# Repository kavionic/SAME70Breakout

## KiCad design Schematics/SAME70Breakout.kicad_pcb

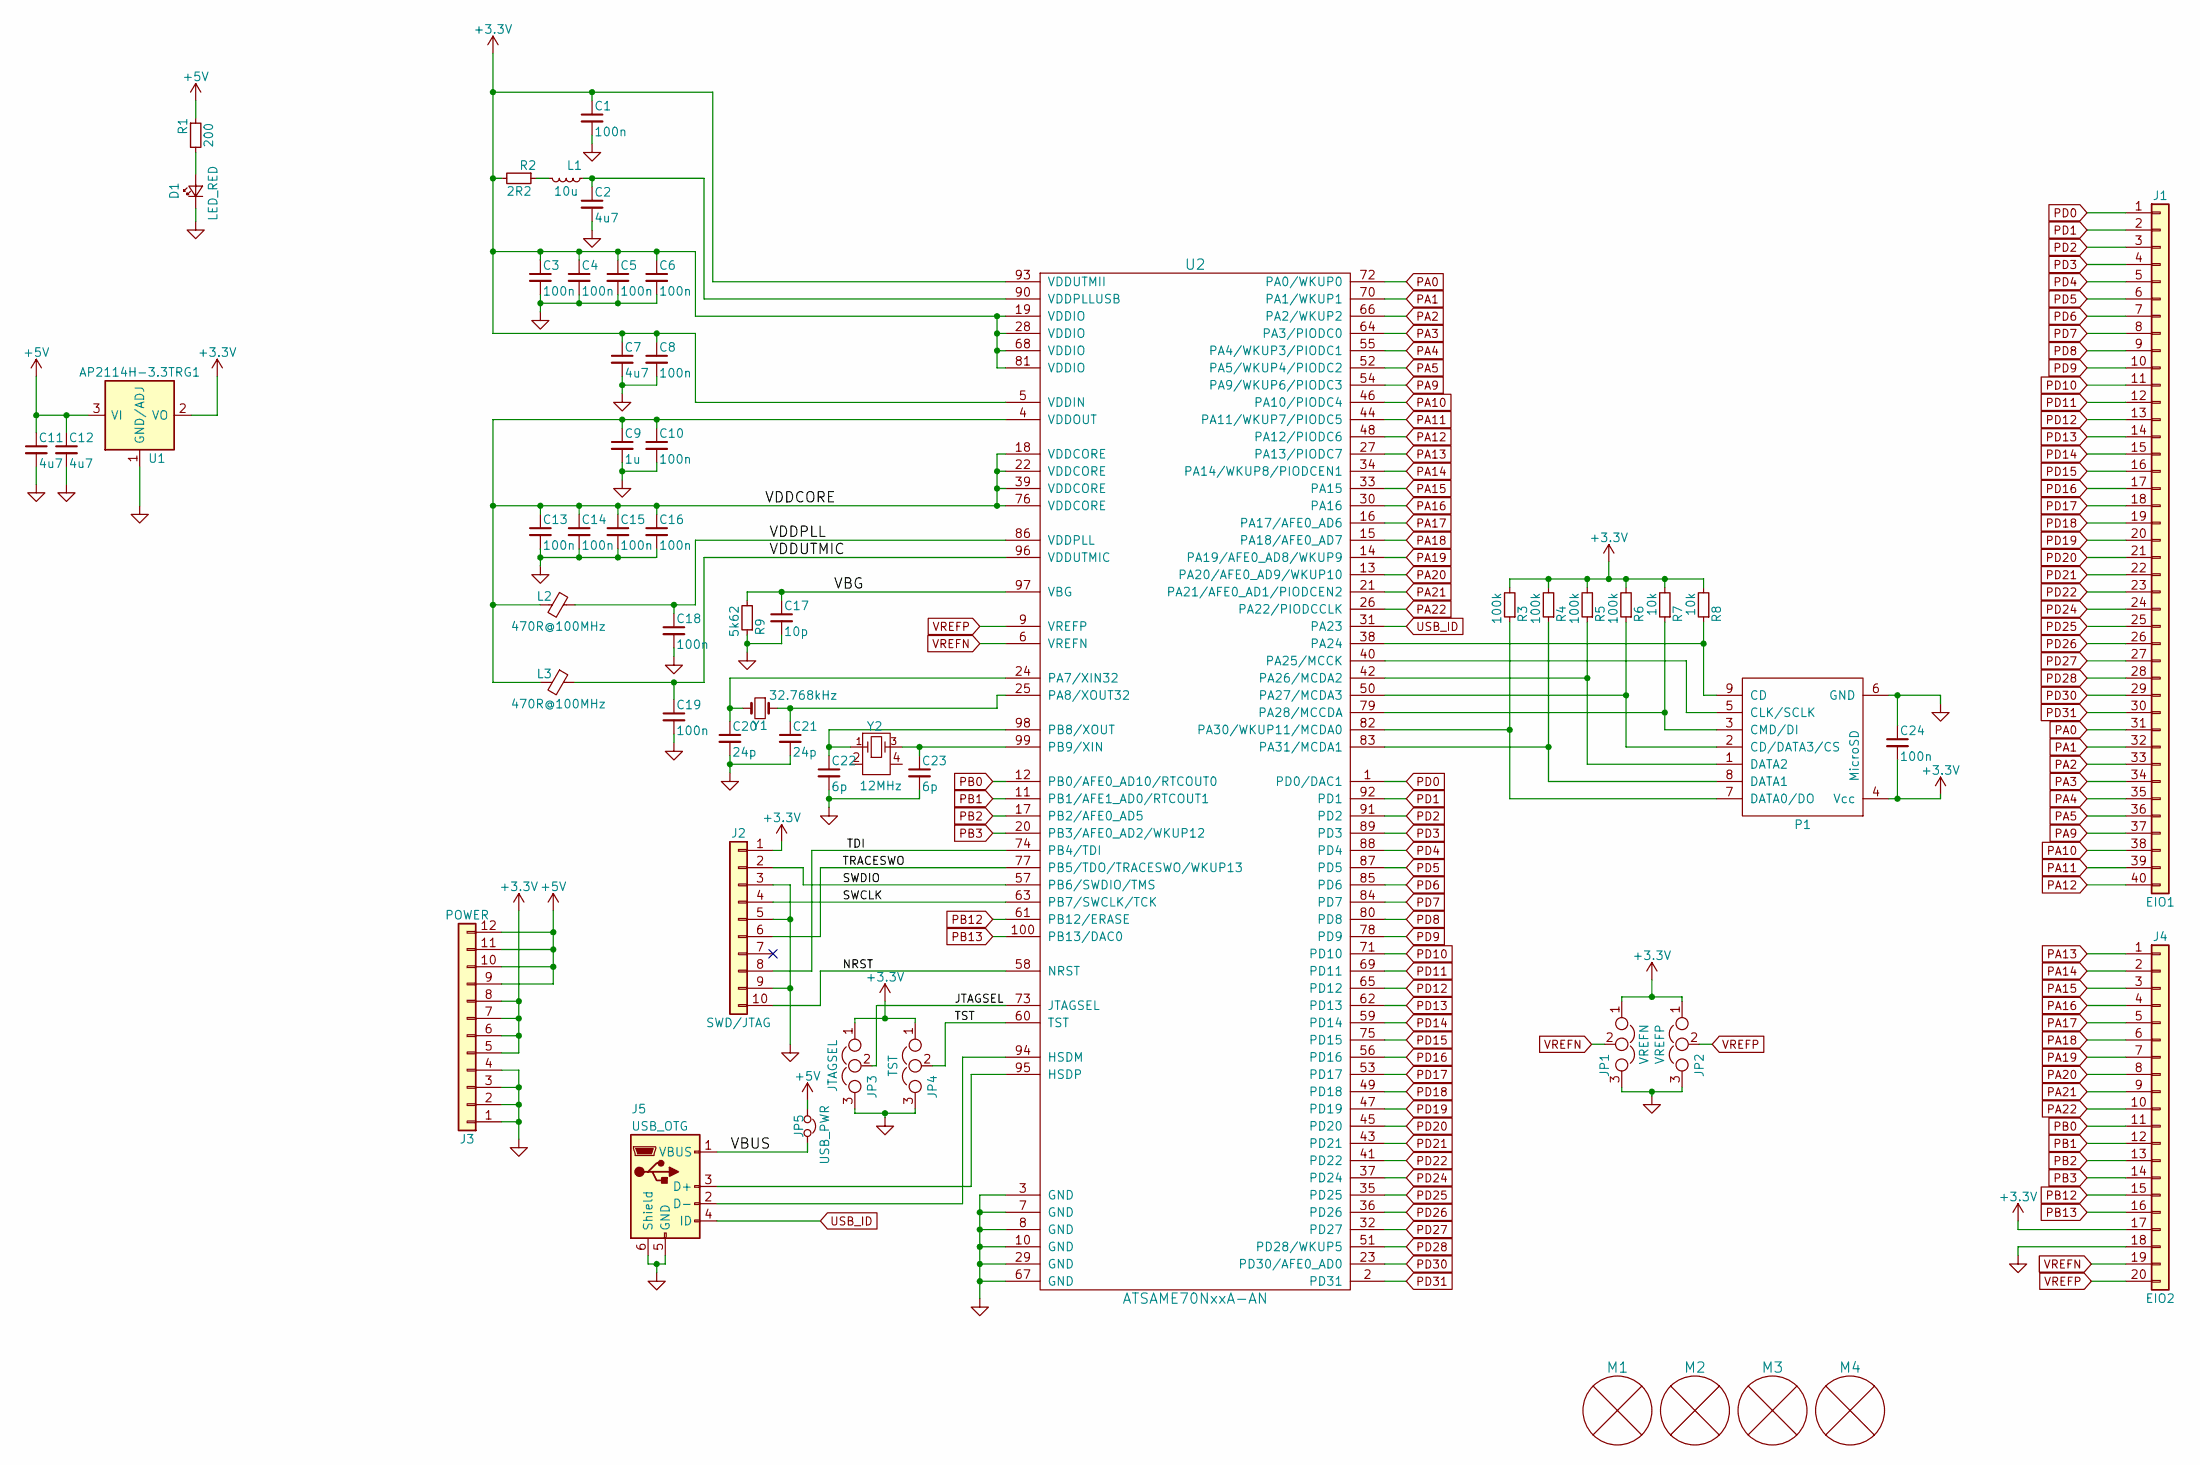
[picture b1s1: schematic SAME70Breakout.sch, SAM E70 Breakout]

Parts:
C1, C3, C4, C5, C6, C8, C10, C13, C14, C15, C16, C18, C19, C24: 100n; C_0603
C2, C7, C11, C12: 4u7; C_0603
C9: 1u; C_0603
C17: 10p; C_0603
C20, C21: 24p; C_0603
C22, C23: 6p; C_0603
D1: LED_RED; LED_0805
J1: EIO1; IDC_Header_Straight_40pins
J2: SWD/JTAG; BoxHeader_Straight_2x05_Pitch1.27mm
J3: POWER; PinHeaderMale_2x06
J4: EIO2; IDC_Header_Straight_20pins
J5: USB_OTG; USB_Micro-B_Molex-105017-0001
JP1: VREFN; PinHeader_1x03
JP2: VREFP; PinHeader_1x03
JP3: JTAGSEL; PinHeader_1x03
JP4: TST; PinHeader_1x03
JP5: USB_PWR; PinHeader_1x02
L1: 10u; L_0805
L2, L3: 470R@100MHz; Choke_SMD_0603_Standard
M1, M2, M3, M4: MountingHole; MH7x3
P1: MicroSD
R1: 200; R_0603
R2: 2R2; R_0603
R3, R4, R5, R6: 100k; R_0603
R7, R8: 10k; R_0603
R9: 5k62; R_0603
U1: AP2114H-3.3TRG1; SOT-223
U2: ATSAME70NxxA-AN; LQFP-100_14x14mm_Pitch0.5mm
Y1: 32.768kHz; Crystal_SMD_3215-2pin_3.2x1.5mm
Y2: 12MHz; Crystal-3225

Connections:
+3V3: C1.1, C3.1, C4.1, C5.1, C6.1, C7.1, C8.1, C24.2, J2.1, J3.5, J3.6, J3.7, J3.8, J4.17, JP1.1, JP2.1, JP3.1, JP4.1, P1.4 (Vcc), R2.2, R3.2, R4.2, R5.2, R6.2, R7.2, R8.2, U1.2 (VO), U1.4 (VO), U2.5 (VDDIN), U2.19 (VDDIO), U2.28 (VDDIO), U2.68 (VDDIO), U2.81 (VDDIO), U2.93 (VDDUTMII)
+5V: C11.1, C12.1, J3.9, J3.10, J3.11, J3.12, JP5.1, R1.1, U1.3 (VI)
/JTAGSEL: JP3.2, U2.73 (JTAGSEL)
/NRST: J2.10, U2.58 (NRST)
/SWCLK: J2.4, U2.63 (PB7/SWCLK/TCK)
/SWDIO: J2.2, U2.57 (PB6/SWDIO/TMS)
/TDI: J2.8, U2.74 (PB4/TDI)
/TRACESWO: J2.6, U2.77 (PB5/TDO/TRACESWO/WKUP13)
/TST: JP4.2, U2.60 (TST)
/VBG: C17.1, R9.2, U2.97 (VBG)
/VBUS: J5.1 (VBUS), JP5.2
/VDDCORE: C9.1, C10.1, C13.1, C14.1, C15.1, C16.1, L2.2, L3.2, U2.4 (VDDOUT), U2.18 (VDDCORE), U2.22 (VDDCORE), U2.39 (VDDCORE), U2.76 (VDDCORE)
/VDDPLL: C18.1, L2.1, U2.86 (VDDPLL)
/VDDUTMIC: C19.1, L3.1, U2.96 (VDDUTMIC)
GND: C1.2, C2.2, C3.2, C4.2, C5.2, C6.2, C7.2, C8.2, C9.2, C10.2, C11.2, C12.2, C13.2, C14.2, C15.2, C16.2, C17.2, C18.2, C19.2, C20.2, C21.2, C22.2, C23.2, C24.1, D1.1 (K), J2.3, J2.5, J2.9, J3.1, J3.2, J3.3, J3.4, J4.18, J5.5 (GND), J5.6 (Shield), JP1.3, JP2.3, JP3.3, JP4.3, P1.6 (GND), P1.10 (GND), P1.11 (GND), P1.12 (GND), P1.13 (GND), R9.1, U1.1 (GND/ADJ), U2.3 (GND), U2.7 (GND), U2.8 (GND), U2.10 (GND), U2.29 (GND), U2.67 (GND)
unnamed: C2.1, L1.1, U2.90 (VDDPLLUSB)
unnamed: C20.1, U2.24 (PA7/XIN32), Y1.2
unnamed: C21.1, U2.25 (PA8/XOUT32), Y1.1
unnamed: C22.1, U2.98 (PB8/XOUT), Y2.1 (X1)
unnamed: C23.1, U2.99 (PB9/XIN), Y2.3 (X2)
unnamed: D1.2 (A), R1.2
unnamed: J5.2 (D-), U2.94 (HSDM)
unnamed: J5.3 (D+), U2.95 (HSDP)
unnamed: L1.2, R2.1
unnamed: P1.1 (DATA2), R5.1, U2.42 (PA26/MCDA2)
unnamed: P1.2 (CD/DATA3/CS), R6.1, U2.50 (PA27/MCDA3)
unnamed: P1.3 (CMD/DI), R7.1, U2.79 (PA28/MCCDA)
unnamed: P1.5 (CLK/SCLK), U2.40 (PA25/MCCK)
unnamed: P1.7 (DATA0/DO), R3.1, U2.82 (PA30/WKUP11/MCDA0)
unnamed: P1.8 (DATA1), R4.1, U2.83 (PA31/MCDA1)
unnamed: P1.9 (CD), R8.1, U2.38 (PA24)
PA0: J1.31, U2.72 (PA0/WKUP0)
PA1: J1.32, U2.70 (PA1/WKUP1)
PA2: J1.33, U2.66 (PA2/WKUP2)
PA3: J1.34, U2.64 (PA3/PIODC0)
PA4: J1.35, U2.55 (PA4/WKUP3/PIODC1)
PA5: J1.36, U2.52 (PA5/WKUP4/PIODC2)
PA9: J1.37, U2.54 (PA9/WKUP6/PIODC3)
PA10: J1.38, U2.46 (PA10/PIODC4)
PA11: J1.39, U2.44 (PA11/WKUP7/PIODC5)
PA12: J1.40, U2.48 (PA12/PIODC6)
PA13: J4.1, U2.27 (PA13/PIODC7)
PA14: J4.2, U2.34 (PA14/WKUP8/PIODCEN1)
PA15: J4.3, U2.33 (PA15)
PA16: J4.4, U2.30 (PA16)
PA17: J4.5, U2.16 (PA17/AFE0_AD6)
PA18: J4.6, U2.15 (PA18/AFE0_AD7)
PA19: J4.7, U2.14 (PA19/AFE0_AD8/WKUP9)
PA20: J4.8, U2.13 (PA20/AFE0_AD9/WKUP10)
PA21: J4.9, U2.21 (PA21/AFE0_AD1/PIODCEN2)
PA22: J4.10, U2.26 (PA22/PIODCCLK)
PB0: J4.11, U2.12 (PB0/AFE0_AD10/RTCOUT0)
PB1: J4.12, U2.11 (PB1/AFE1_AD0/RTCOUT1)
PB2: J4.13, U2.17 (PB2/AFE0_AD5)
PB3: J4.14, U2.20 (PB3/AFE0_AD2/WKUP12)
PB12: J4.15, U2.61 (PB12/ERASE)
PB13: J4.16, U2.100 (PB13/DAC0)
PD0: J1.1, U2.1 (PD0/DAC1)
PD1: J1.2, U2.92 (PD1)
PD2: J1.3, U2.91 (PD2)
PD3: J1.4, U2.89 (PD3)
PD4: J1.5, U2.88 (PD4)
PD5: J1.6, U2.87 (PD5)
PD6: J1.7, U2.85 (PD6)
PD7: J1.8, U2.84 (PD7)
PD8: J1.9, U2.80 (PD8)
PD9: J1.10, U2.78 (PD9)
PD10: J1.11, U2.71 (PD10)
PD11: J1.12, U2.69 (PD11)
PD12: J1.13, U2.65 (PD12)
PD13: J1.14, U2.62 (PD13)
PD14: J1.15, U2.59 (PD14)
PD15: J1.16, U2.75 (PD15)
PD16: J1.17, U2.56 (PD16)
PD17: J1.18, U2.53 (PD17)
PD18: J1.19, U2.49 (PD18)
PD19: J1.20, U2.47 (PD19)
PD20: J1.21, U2.45 (PD20)
PD21: J1.22, U2.43 (PD21)
PD22: J1.23, U2.41 (PD22)
PD24: J1.24, U2.37 (PD24)
PD25: J1.25, U2.35 (PD25)
PD26: J1.26, U2.36 (PD26)
PD27: J1.27, U2.32 (PD27)
PD28: J1.28, U2.51 (PD28/WKUP5)
PD30: J1.29, U2.23 (PD30/AFE0_AD0)
PD31: J1.30, U2.2 (PD31)
USB_ID: J5.4 (ID), U2.31 (PA23)
VREFN: J4.19, JP1.2, U2.6 (VREFN)
VREFP: J4.20, JP2.2, U2.9 (VREFP)

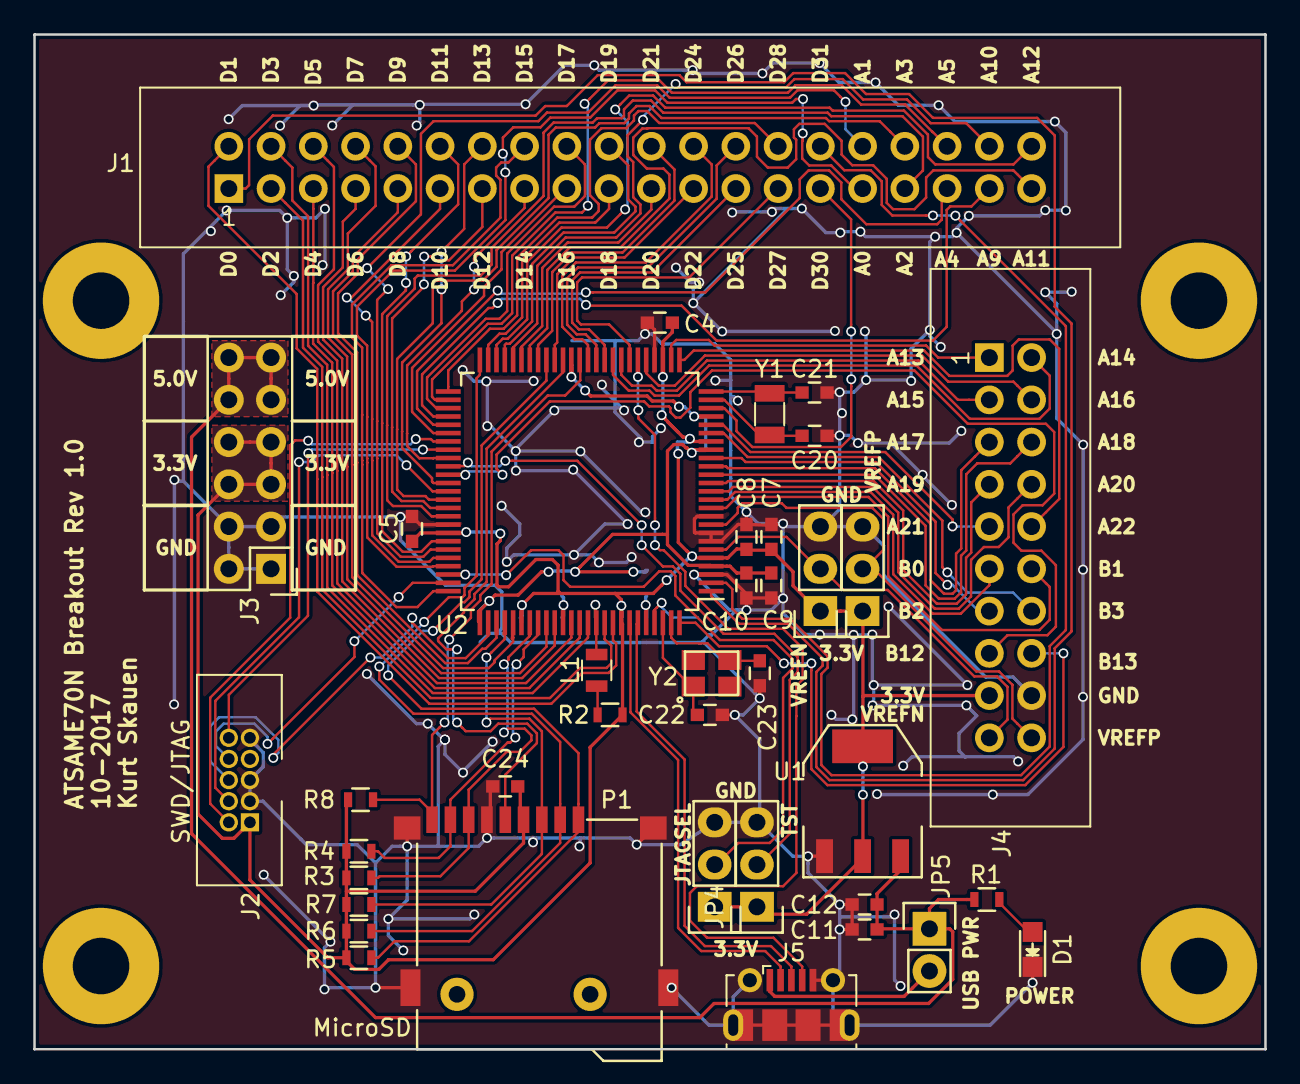
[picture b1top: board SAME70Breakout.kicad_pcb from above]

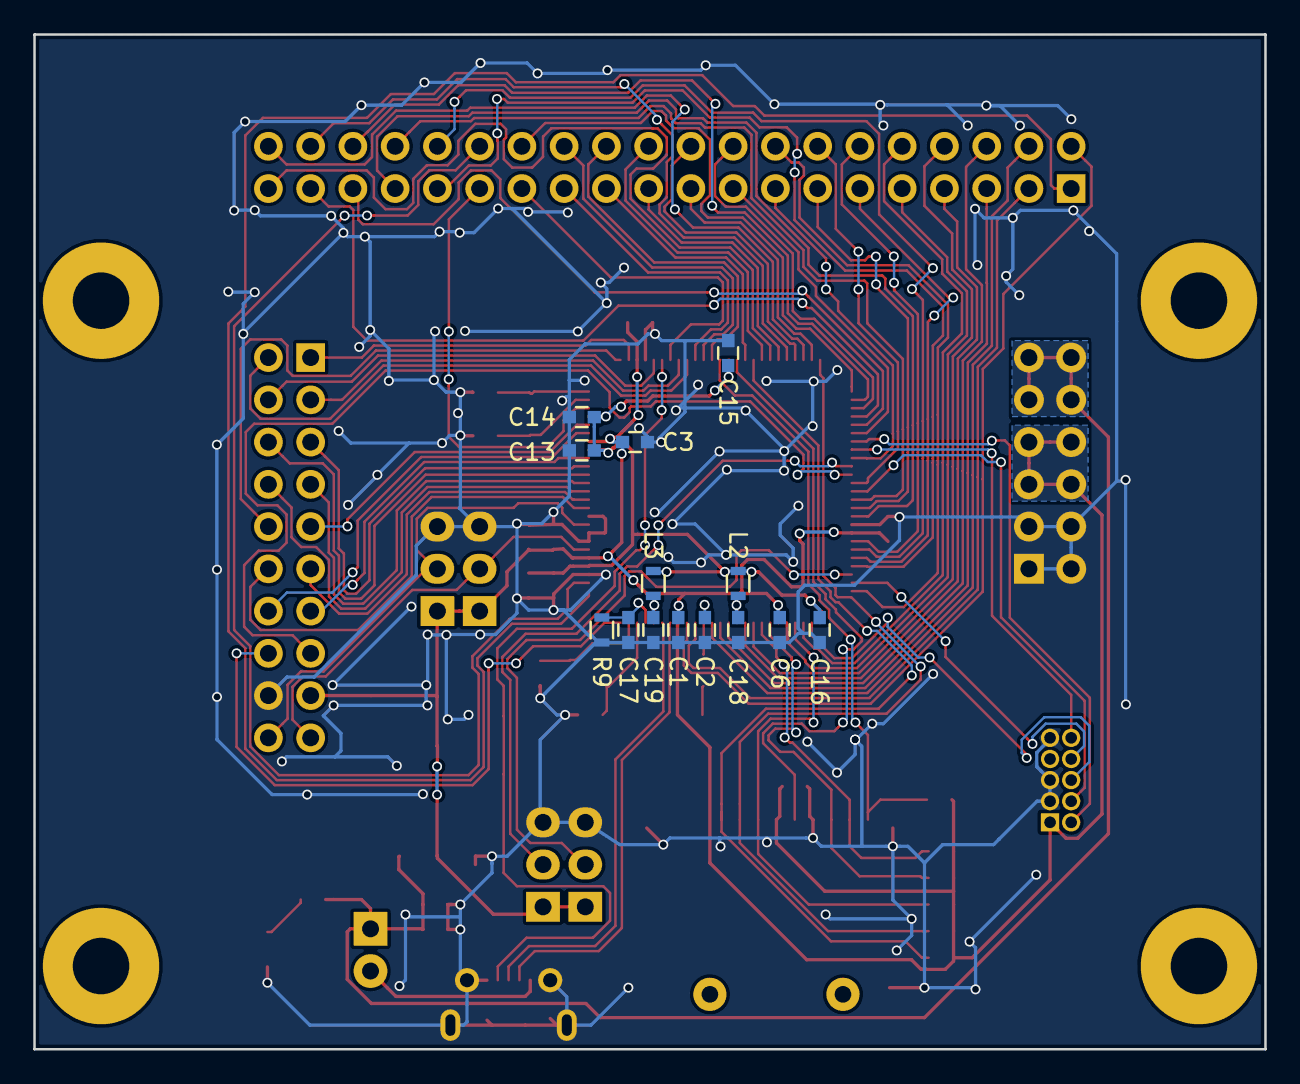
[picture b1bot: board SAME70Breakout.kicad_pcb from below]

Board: 2 copper layers, 74.0 x 61.0 mm, 56 parts (14 on the bottom side), 90 nets.

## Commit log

2017-10-17 :boom::camel: Added .gitattributes
2017-10-17 Initial version of the Atmel SAM E70 development board.
    Small development board for the SAM E70 ARM based MCU. Includes crystals
    for main and realtime clock, a micro USB port, and a MicroSD card slot.
    As well as connectors for SWD/JTAG, power, and general IO.
